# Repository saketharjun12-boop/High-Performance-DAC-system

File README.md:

# High-Performance Mixed-Signal Headphone DAC

**AK4191EQ + AK4499EX + ESP32-S3 | KiCad | Low-Noise Power | High-Impedance Headphones**

A custom mixed-signal headphone DAC/amplifier designed around the **AK4191EQ digital modulator** and **AK4499EX DAC**, with a focus on low-noise analog power, current-to-voltage conversion, differential analog processing, and high-impedance headphone drive.

> **Project status:** PCB routing is **not complete**. Routing is currently complete **through Stage 2 only**. Later analog/output and remaining power-routing sections are still in progress.

---

## Project Overview

Primary signal chain:

```text
Digital Source
    |
AK4191EQ Digital Modulator
    |
AK4499EX DAC
    |
OPA1612 I/V Conversion
    |
Low-Pass / Differential Summing
    |
OPA1622 Headphone Driver
    |
Output Mute Relay
    |
6.35 mm TRS Headphone Jack
```

Control is provided by an **ESP32-S3**, including I2C configuration and future power-sequencing / relay-control functionality.

---

## Main Components

| Function | Component |
|---|---|
| Digital modulator | AK4191EQ |
| DAC | AK4499EX |
| Controller | ESP32-S3 |
| I/V conversion | OPA1612 |
| Headphone output stage | OPA1622 |
| 5 V to 5.8 V boost | TPS610891 |
| Ultra-low-noise 5VA LDO | LT3045 |
| Bipolar analog supply | TPS65131 |
| Output muting | DPDT relay |
| Output connector | 6.35 mm TRS jack |

---

## Current Project Status

- [x] Overall architecture defined
- [x] Major components selected
- [x] AK4191EQ / AK4499EX architecture
- [x] I/V conversion stage
- [x] Differential / headphone output stage
- [x] Relay-based output mute
- [x] 5VA power architecture
- [x] +/-15 V rail architecture
- [x] Initial power budget
- [x] TPS610891 design calculations
- [x] LT3045 calculations
- [x] Initial +/-15 V / headphone-load budget
- [x] Initial trace-width and via-sizing methodology
- [x] PCB routing through **Stage 3**
- [ ] Remaining PCB routing
- [ ] Final ERC / DRC
- [ ] Final BOM freeze
- [ ] Gerber generation
- [ ] Fabrication
- [ ] Assembly
- [ ] Board bring-up
- [ ] Electrical validation
- [ ] Audio measurements

---

# Power Architecture

```text
USB-C 5 V
   |
   +---- TPS610891 ----> 5.8 V ----> LT3045 ----> 5VA
   |
   +---- TPS65131 ----> +15 V / -15 V
   |
   +---- 3.3 V Regulator ----> ESP32-S3 / clocks / logic
   |
   +---- 1.2 V Regulator ----> AK4191EQ core
```

The **5VA** rail is reserved for the AK4499EX analog/reference supply domains.

---

# Power Budget

The power budget is used to verify regulator capability, estimate upstream USB-C current, and provide starting values for power-trace and via sizing.

## 5VA Analog Rail

| Device / Supply Domain | Typical Current |
|---|---:|
| AK4499EX VDDL + VDDR | 18 mA |
| AK4499EX VREFHL + VREFHR | 46 mA |
| AK4499EX AVDD | 3 mA |
| **AK4499EX subtotal** | **67 mA** |
| LT3045 operating-current provision | ~3 mA |
| **Approximate subtotal** | **~70 mA** |

30% design margin:

```text
70 mA x 1.30 = 91 mA
```

Rounded target:

**5VA design current = 100 mA**

The LT3045 is rated for **500 mA**, so the present load estimate has substantial current margin.

## +15 V and -15 V Rails

| Device | Approximate Current |
|---|---:|
| OPA1622, two channels | 6.76 mA |
| OPA1612 stages | 18 mA |
| **Quiescent subtotal** | **24.76 mA** |

The headphone load adds output-stage rail current. A provisional design target of **75 mA per rail** is derived below.

## 3.3 V Rail

| Component / Function | Peak / Estimated Current |
|---|---:|
| ESP32-S3-MINI-1U peak RF transient assumption | 355 mA |
| AK4191EQ 3.3 V domain(s) | ~5 mA |
| Master-clock oscillators | ~20 mA total |
| 74LVC1G3157 MUX | ~2 mA |
| Pull-ups / passive leakage | ~3 mA |
| **Estimated peak subtotal** | **385 mA** |

Using 50% margin for ESP32 burst current:

```text
385 mA x 1.5 = 577.5 mA
```

Rounded target:

**3.3 V design current = 600 mA**

## 1.2 V Rail

AK4191EQ DVDD core:

- Typical: ~18 mA
- Max / peak design value: ~25 mA

30% margin:

```text
25 mA x 1.30 = 32.5 mA
```

Rounded target:

**1.2 V design current = 40 mA**

---

# TPS610891 Boost Converter Calculations

The TPS610891 creates approximately **5.8 V** from the USB-C 5 V input so the LT3045 has headroom to regulate to 5.0VA.

## Design Targets

| Parameter | Value |
|---|---:|
| VIN | 5.0 V nominal |
| VOUT | 5.8 V |
| IOUT | 100 mA |
| fSW | ~2 MHz |
| Provisional efficiency | 85% |
| Provisional inductor | 2.2 uH |

## Feedback Divider

The PWM feedback reference is approximately 1.212 V.

```text
VOUT = VREF(1 + R1/R2)
```

Choose:

```text
R2 = 100 kOhm
```

Then:

```text
R1 = R2(VOUT/VREF - 1)
R1 = 100k(5.8/1.212 - 1)
R1 ~= 378.5 kOhm
```

Practical selection:

- **R1 ~= 379 kOhm**
- **R2 = 100 kOhm**

## Switching-Frequency Resistor

Using the TPS610891 frequency-setting equation:

```text
RFREQ = 4(1/fSW - tDELAY*VOUT/VIN) / CFREQ
```

with:

```text
fSW = 2 MHz
tDELAY = 86 ns
CFREQ = 24 pF
VOUT = 5.8 V
VIN = 5.0 V
```

Calculated:

**RFREQ ~= 66.7 kOhm**

## Average Inductor Current

```text
IDC = (VOUT*IOUT)/(VIN*eta)
IDC = (5.8*0.1)/(5*0.85)
IDC ~= 136.5 mA
```

## Inductor Ripple Current

```text
IPP = 1 / [L(1/(VOUT-VIN) + 1/VIN)fSW]
```

For L = 2.2 uH:

**IPP ~= 157 mA p-p**

## Peak Inductor Current

```text
IL,peak = IDC + IPP/2
IL,peak = 136.5 mA + 78.5 mA
IL,peak ~= 215 mA
```

Worst-case inductance check using a 30% reduction:

```text
Lmin = 2.2 uH x 0.7 = 1.54 uH
```

A shielded power inductor rated around **1 A or higher** provides generous margin relative to the present calculated peak.

## Equivalent Output Load Resistance

```text
RO = VOUT/IOUT = 5.8/0.1 = 58 Ohm
```

**RO = 58 Ohm**

## Duty Cycle

Using the small-signal equation:

```text
D = 1 - (VIN*eta)/VOUT
D = 1 - (5*0.85)/5.8
D ~= 0.267
```

**D ~= 26.7%**

## Provisional Compensation Assumptions

```text
CO effective = 45 uF
RESR = 3 mOhm
L = 2.2 uH
fSW = 2 MHz
eta = 85%
IOUT = 100 mA
```

These values are provisional until the final capacitor and inductor part numbers are selected.

## Output Pole

```text
fP = 2/(2*pi*RO*CO)
fP ~= 122 Hz
```

## ESR Zero

```text
fESRZ = 1/(2*pi*RESR*CO)
fESRZ ~= 1.18 MHz
```

## Right-Half-Plane Zero

```text
fRHPZ = RO(1-D)^2/(2*pi*L)
fRHPZ ~= 2.25 MHz
```

## Crossover Frequency

Guideline:

```text
fC <= min(fSW/10, fRHPZ/5)
```

```text
fSW/10 = 200 kHz
fRHPZ/5 ~= 450 kHz
```

Provisional crossover:

**fC = 200 kHz**

## Compensation Resistor R5

```text
R5 = [2*pi*VOUT*Rsense*fC*CO] / [(1-D)*VREF*GEA]
```

Using:

```text
Rsense = 0.08 Ohm
VREF = 1.212 V
GEA = 190 uS
```

Calculated:

**R5 ~= 155.5 kOhm**

Practical provisional values:

- 154 kOhm
- 158 kOhm

## Compensation Capacitor C5

```text
C5 = RO*CO/(2*R5)
C5 ~= 8.39 nF
```

Practical provisional value:

**C5 ~= 8.2 nF**

## Compensation Capacitor C6

```text
C6 = RESR*CO/R5
C6 ~= 0.87 pF
```

Because the calculated value is below 10 pF:

**C6 = DNP / Open**

> The compensation network is provisional and should be recalculated using the final inductor, effective output capacitance, capacitor ESR, switching frequency, efficiency, and load.

---

# LT3045 5VA Rail Calculations

Architecture:

```text
5.8 V --> LT3045 --> 5.0VA
```

## SET Resistor

The SET pin sources approximately 100 uA.

```text
RSET = VOUT/ISET
RSET = 5.0/(100 uA)
RSET = 50 kOhm
```

Practical precision value:

**RSET = 49.9 kOhm**

## LDO Dissipation

At the 100 mA design target:

```text
PLDO = (VIN-VOUT)IOUT
PLDO = (5.8-5.0)(0.1)
PLDO = 0.08 W
```

## Power-Good Divider

The PGFB comparator threshold is approximately 300 mV.

Desired Power Good threshold:

```text
VTRIP ~= 4.5 V
```

Choose:

```text
RBOTTOM = 49.9 kOhm
```

Then:

```text
RTOP = RBOTTOM(VTRIP/VPGFB - 1)
RTOP = 49.9k(4.5/0.3 - 1)
RTOP ~= 698.6 kOhm
```

Practical values:

- **RTOP ~= 700 kOhm**
- **RBOTTOM = 49.9 kOhm**

## PG Pull-Up

For ESP32 3.3 V logic:

**RPG = 10 kOhm to 3.3 V**

## Provisional LT3045 Capacitors

- Input: **10 uF + 100 nF**
- SET: **4.7 uF** optional low-noise capacitor
- Output: **22 uF + 100 nF**

Final values should be verified against the final LT3045 implementation.

---

# TPS65131 +/-15 V Rail Calculations

Current design targets:

- **+15 V, 75 mA**
- **-15 V, 75 mA**

## Output Power

```text
POUT = 15I+15 + 15I-15
POUT = 15(0.075) + 15(0.075)
POUT = 2.25 W
```

## 5 V Input-Power Estimate

Assume provisional efficiency:

```text
eta = 80%
```

Then:

```text
PIN = POUT/eta
PIN = 2.25/0.8
PIN = 2.8125 W
```

Input current from 5 V:

```text
IIN,5V = PIN/5
IIN,5V = 2.8125/5
IIN,5V ~= 563 mA
```

**Provisional TPS65131 5 V input requirement ~= 0.56 A**

---

# Headphone Load Calculations

Target class: high-impedance headphones such as a nominal **300 Ohm** load.

The AK4499EX documentation indicates approximately:

- **4.6 Vrms** after individual I/V conversion around signal common
- approximately **9.2 Vrms** after external differential summing

## RMS Headphone Current

```text
IRMS = VRMS/RHP
IRMS = 9.2/300
IRMS ~= 30.7 mA/channel
```

## Peak Current

```text
IPEAK = sqrt(2)*IRMS
IPEAK ~= 43.4 mA/channel
```

## Output Power

```text
POUT = VRMS^2/RHP
POUT = 9.2^2/300
POUT ~= 0.282 W/channel
```

## Approximate Rail-Current Contribution

For a sinusoidal class-AB approximation:

```text
Irail,load ~= IPEAK/pi
Irail,load ~= 13.8 mA/channel
```

Stereo:

```text
Irail,load,stereo ~= 27.6 mA/rail
```

Add amplifier quiescent current:

```text
24.76 + 27.6 = 52.36 mA/rail
```

Apply 30% margin:

```text
52.36 x 1.30 = 68.1 mA/rail
```

Rounded design target:

**75 mA per rail**

---

# Trace Width Calculations

Power-trace width is based on current, copper thickness, route length, acceptable voltage drop, temperature rise, and fabrication limits.

Copper resistivity:

```text
rho ~= 1.72e-8 Ohm*m
```

For 1 oz copper:

```text
t ~= 35 um
```

## Trace Resistance

```text
Rtrace = rho*L/(w*t)
```

## Voltage Drop

```text
Vdrop = I*Rtrace
```

## Power Loss

```text
Ploss = I^2*Rtrace
```

## Width From Voltage-Drop Requirement

```text
w = rho*L*I/(t*Vdrop,max)
```

## 5VA Example

Assume:

```text
I = 0.1 A
L = 50 mm = 0.05 m
Vdrop,max = 5 mV = 0.005 V
t = 35 um
```

Calculated:

```text
w ~= 0.49 mm
```

Practical provisional width:

**5VA = 0.50 mm**

## +/-15 V Example

Using:

```text
I = 75 mA
L = 50 mm
Vdrop,max = 5 mV
```

Calculated width is approximately 0.37 mm.

Practical provisional choice:

**+15 V / -15 V = 0.50 mm**

## 3.3 V Main Distribution

With a 600 mA design target, the main 3.3 V trunk is provisionally assigned:

**3.3 V main = ~0.8 mm**

Individual low-current branches do not need to remain 0.8 mm.

## USB 5 V

Provisional initial class:

**USB 5 V = 1.0-1.2 mm**

## Headphone Output

The 300 Ohm load current is modest, so the wider trace primarily reduces added series resistance and provides robust routing.

**Headphone output = ~0.8 mm**

---

# Via Sizing

## Standard Signal Via

```text
Diameter: 0.60 mm
Drill:    0.30 mm
```

Used for digital signals, I2C, I2S, ordinary analog signals, ground stitching, and low-current branches.

## Power Via

```text
Diameter: 0.80 mm
Drill:    0.40 mm
```

Used for 5VA, +/-15 V, and main 3.3 V power transitions.

## Higher-Current USB Via

```text
Diameter: 1.00 mm
Drill:    0.50 mm
```

or multiple smaller vias in parallel.

Multiple vias are preferred where higher current or lower inductance is desired.

---

# Net Classes

| Net Class | Clearance | Width | Via | Drill |
|---|---:|---:|---:|---:|
| Signal | 0.20 mm | 0.20 mm | 0.60 mm | 0.30 mm |
| Clock | 0.20 mm | 0.20 mm | 0.60 mm | 0.30 mm |
| I2S | 0.20 mm | 0.20 mm | 0.60 mm | 0.30 mm |
| Analog Signal | 0.20 mm | 0.20-0.25 mm | 0.60 mm | 0.30 mm |
| 5VA | 0.20 mm | 0.50 mm | 0.80 mm | 0.40 mm |
| +15 V | 0.20 mm | 0.50 mm | 0.80 mm | 0.40 mm |
| -15 V | 0.20 mm | 0.50 mm | 0.80 mm | 0.40 mm |
| 3V3 Main | 0.20 mm | ~0.80 mm | 0.80 mm | 0.40 mm |
| 1V2 | 0.20 mm | 0.30-0.50 mm | 0.60 mm | 0.30 mm |
| USB Power | 0.20-0.25 mm | 1.0-1.2 mm | 1.00 mm | 0.50 mm |
| Headphone Out | 0.20 mm | 0.80 mm | 0.80 mm | 0.40 mm |

These values should be checked against the final PCB manufacturer's design rules.

---

# Critical Signal Lengths

| Connection | Target |
|---|---:|
| AK4499EX IOUT to OPA1612 input | ideally <5-10 mm |
| OPA1612 feedback loop | ideally <5 mm |
| OPA1622 feedback / summing network | ideally <5-10 mm |
| 100 nF decoupling capacitor | approximately 1-3 mm from supply pin where practical |
| TPS610891 SW to inductor | minimum practical length |
| TPS65131 switch nodes | minimum practical length |
| LT3045 SET / OUTS | preferably <5-10 mm |
| MCLK | preferably <25-30 mm |
| BCLK / LRCK / SDATA | short; ~10 mm BCLK is excellent |

---

# Repository Folders

```text
High_Performance_DAC_Portfolio/
|
|-- README.md
|-- PCB_Files/
|-- Schematics/
|-- Images/
|-- Handwritten_Calculations/
|-- Datasheets/
|-- BOM/
`-- Gerbers/
```

## Schematic Images and PCB progress

## Total Circuit

## Stage 1

## Stage 2

## Stage 3

## Stage 4

## USB-C Interface

## Boost Inverter and Boost Regulator

## PCB progress Stage 1 and Stage 2

---

# Planned Validation

After fabrication:

- Verify 5.8 V boost output
- Verify 5VA regulation
- Measure 5VA ripple
- Measure +15 V and -15 V ripple
- Verify startup sequencing
- Verify Power Good behavior
- Verify relay mute timing
- Measure DAC DC offsets
- Verify maximum headphone output
- Measure frequency response
- Measure FFT / noise floor
- Measure THD+N
- Measure output impedance
- Evaluate thermal performance

---

# Future Work

- Complete PCB routing after Stage 2
- Recalculate power-trace voltage drop using actual routed lengths
- Freeze exact capacitor and inductor manufacturer part numbers
- Recalculate TPS610891 compensation using final effective capacitance and ESR
- Perform final regulator thermal checks
- Run ERC and DRC
- Generate Gerbers
- Fabricate and assemble the PCB
- Perform bring-up and measurement
- Add measurement plots and final PCB renders to this README

---

# Disclaimer

This repository documents an **in-progress engineering project**.

The present PCB routing is not complete, and the design has not yet been fabricated or electrically validated. Several calculated values are provisional and will be updated after the final BOM, PCB routing, and measured prototype data are available.

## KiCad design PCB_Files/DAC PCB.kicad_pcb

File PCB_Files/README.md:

Place KiCad PCB/project files here.

Current PCB routing is incomplete and only complete through Stage 3.

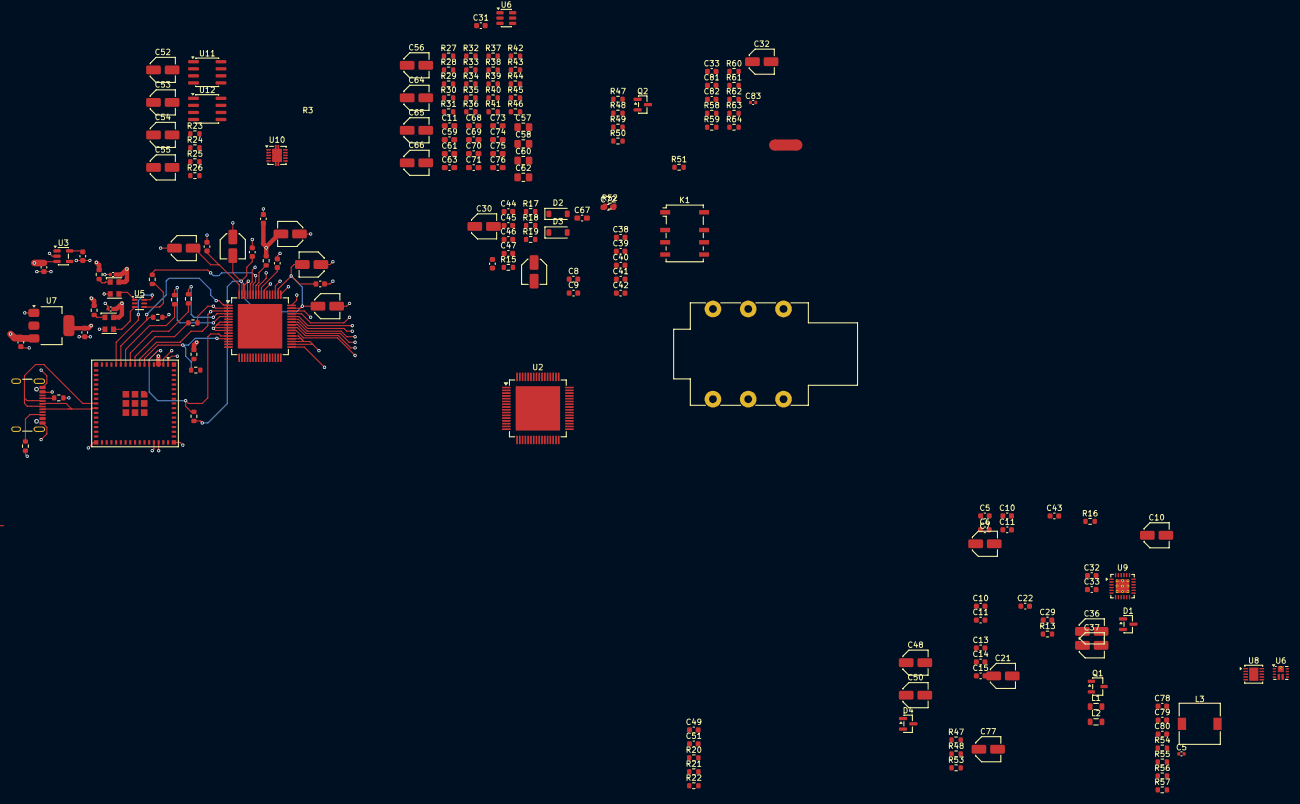
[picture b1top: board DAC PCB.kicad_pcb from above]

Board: 4 copper layers, 184 parts (0 on the bottom side), 109 nets.

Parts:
C1, C2, C5#2: 0.1uF; C_0402_1005Metric
C3, C4, C5, C6, C8, C9, C10, C10#2, C11#2, C11#3, C12, C14, C16: 1uF; C_0603_1608Metric
C7, C10#3: 1uF; C_Elec_4x5.4
C11, C59, C61, C63: 100nF; C_0603_1608Metric_Pad1.08x0.95mm_HandSolder
C13, C15: 10uF; C_0603_1608Metric
C17, C19, C21, C26, C28: 10F; C_Elec_4x5.4
C18, C20, C22, C24, C27, C29, C33#2: 0.1F; C_0603_1608Metric
C23, C30, C32#2, C36, C50, C52, C54: 10uF; C_Elec_4x5.4
C25: 22F; C_0603_1608Metric
C31, C33, C34, C49, C51, C81: 0.1uF; C_0603_1608Metric
C32: 10F; C_0603_1608Metric
C35, C48: 2200uF; C_Elec_4x5.4
C37, C53, C55, C77: 0.1uF; C_Elec_4x5.4
C38, C40, C46: 4.7uF; C_0603_1608Metric
C39: 100nF; C_0603_1608Metric
C41, C45, C78, C79, C80, C82: 22uF; C_0603_1608Metric
C42: 6.8pF; C_0603_1608Metric
C43: 220nF; C_0603_1608Metric
C44: 7.5pF; C_0603_1608Metric
C47: 10nF; C_0603_1608Metric
C56, C64, C65, C66: 180pF; C_Elec_4x5.4
C57, C58, C60, C62: 10uF; C_0805_2012Metric_Pad1.18x1.45mm_HandSolder
C67, C68, C69, C70, C71, C72: 1nF; C_0603_1608Metric_Pad1.08x0.95mm_HandSolder
C73, C74, C75, C76: 470pF; C_0603_1608Metric_Pad1.08x0.95mm_HandSolder
C83: 8.5nF; C_0402_1005Metric
D1, D4: BZX84Cxx; SOT-23
D2, D3: D_Schottky; D_SOD-123
J1: USB_C_Receptacle_USB2.0_16P; USB_C_Receptacle_GCT_USB4105-xx-A_16P_TopMnt_Horizontal
J2: AudioJack3_Switch; Jack_6.35mm_Neutrik_NMJ6HHD2_Horizontal
K1: Relay_DPDT; Relay_DPDT_Omron_G6K-2F-Y
L1, L2: 4.7uH; L_0805_2012Metric
L3: 2.2uH; L_7.3x7.3_H4.5
NT1: NetTie_2; NetTie-2_SMD_Pad2.0mm
Q1: Q_PMOS_GSD; SOT-23-3
Q2: MMBT3904; SOT-23
R1, R2, R7, R8, R14, R21: 4700; R_0603_1608Metric
R3, R4, R5, R10: 33; R_0603_1608Metric
R6, R9, R13, R20, R22, R47, R48, R53, R63: 10000; R_0603_1608Metric
R11, R12: 5100; R_0603_1608Metric
R15, R32, R34, R37, R38: 100; R_0603_1608Metric
R16, R19: 1M; R_0603_1608Metric
R17: 130k; R_0603_1608Metric
R18: 121.2k; R_0603_1608Metric
R23, R24, R25, R26, R41, R42, R45, R46: 2000; R_0603_1608Metric
R27, R28, R29, R30: 360; R_0603_1608Metric
R31, R33, R35, R36: 500; R_0603_1608Metric
R39, R40, R43, R44: 5000; R_0603_1608Metric
R47#2, R48#2, R51, R52: 2.2; R_0603_1608Metric
R49: 2200; R_0603_1608Metric
R50: 100000; R_0603_1608Metric
R54: 66.8k; R_0603_1608Metric
R55: 378.5k; R_0603_1608Metric
R56: 100k; R_0603_1608Metric
R57: 1.03M; R_0603_1608Metric
R58: 30.1k; R_0603_1608Metric
R59: 249; R_0603_1608Metric
R60: 50; R_0603_1608Metric
R61: 49.9k; R_0603_1608Metric
R62: 700k; R_0603_1608Metric
R64: 150k; R_0603_1608Metric
U1, U2: Texas_TQFP-64-1EP_10x10mm_P0.5mm_EP8x8mm_Mask4.44x4.44mm
U3: AP2112K-1.2; SOT-23-5
U4: ESP32-S3-MINI-1U; ESP32-S2-MINI-1U
U5: 74LVC1G3157; SOT-363_SC-70-6
U6: TPS610891; Texas_VQFN-RNR0011A-11
U6#2: MCP4725xxx-xCH; SOT-23-6
U7: AMS1117-3.3; SOT-223-3_TabPin2
U8: LT3045xDD; DFN-10-1EP_3x3mm_P0.5mm_EP1.65x2.38mm
U9: TPS65131RGE; VQFN-24-1EP_4x4mm_P0.5mm_EP2.45x2.45mm_ThermalVias
U10: OPA1622; Texas_S-PVSON-N10
U11, U12: OPA1612AxD; SOIC-8_3.9x4.9mm_P1.27mm
Y1, Y2: XO32; Oscillator_SMD_EuroQuartz_XO32-4Pin_3.2x2.5mm

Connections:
+1.2V: C16.1, C17.2, C18.2, U1.64 (DVDD), U3.5 (VOUT)
+1.8V: C6.1, C7.2, C8.2, C9.2, C10#3.2, C13.1, C14.1, C15.1, C19.2, C20.2, C26.2, C27.2, C28.1, C29.1, C30.2, C31.2, C32#2.1, C33.1, C34.1, C35.1, C36.2, C37.2, C48.1, C49.1, C50.2, C51.2, C52.1, C53.1, C54.1, C55.1, C68.2, C69.1, C71.2, C72.1, C73.1, C75.1, C81.1, C82.2, D1.1 (A), D4.1 (A), J2.S, NT1.2, Q2.2 (E), R1.1, R2.1, R20.2, R21.1, R24.2, R26.2, R42.1, R45.1, R50.1, R58.2, R59.2, R60.2, R61.2, U1.47 (TVDD4), U1.50 (TVDD3), U1.63 (TVDD1), U2.2 (TVDD), U2.21 (VREFHR), U2.22 (VREFHR), U2.23 (VREFHR), U2.27 (VSSR), U2.28 (VSSR), U2.29 (VSSR), U2.34 (DEV1), U2.47 (DEV2), U2.52 (VSSL), U2.53 (VSSL), U2.54 (VSSL), U2.55 (VREFLL), U2.56 (VREFLL), U2.57 (VREFLL), U2.62 (AVSS), U2.64 (DVDD), U8.8 (GND), U8.11 (GND), U10.3 (GND)
+3.3V: C1.2, C2.2, C4.1, C11#3.1, C23.2, C24.2, R7.1, R8.1, R9.1, R13.1, R14.1, R53.1, R63.1, U4.3 (3V3), U7.2 (VO), Y1.4 (V+), Y2.4 (V+)
+5V: C3.1, C5.1, C10#2.1, C12.1, C32.2, C33#2.2, C40.1, C78.1, J1.A4 (VBUS), J1.A9 (VBUS), J1.B4 (VBUS), J1.B9 (VBUS), L3.1, Q1.2 (S), R15.1, U3.1 (VIN), U3.3 (EN), U6.9 (VIN), U6#2.3 (VDD), U7.3 (VI), U9.5 (INN), U9.6 (INN)
+5VA: C30.1, C31.1, C34.2, C35.2, C36.1, C37.1, C48.2, C49.2, C50.1, C51.1, C81.2, C82.1, D1.3 (K), D4.3 (K), R23.1, R25.1, R60.1, R62.1, U2.24 (VREFLR), U2.25 (VREFLR), U2.26 (VREFLR), U2.30 (VDDR), U2.31 (VDDR), U2.32 (VDDR), U2.49 (VDDL), U2.50 (VDDL), U2.51 (VDDL), U2.58 (VREFHL), U2.59 (VREFHL), U2.60 (VREFHL), U2.61 (AVDD), U6#2.1 (VOUT), U8.9 (OUTS), U8.10 (OUT)
+15V: C11.1, C41.1, C42.1, C57.1, C60.1, C61.1, D2.1 (K), R16.2, U9.23 (VPOS), U10.2 (V+), U10.8 (EN), U11.8 (V+), U12.8 (V+)
-15V: C44.2, C45.1, C58.1, C59.1, C62.1, C63.1, D3.2 (A), R19.1, U9.15 (VNEG), U10.4 (V-), U10.11 (V-), U11.4 (V-), U12.4 (V-)
/BCKO: U1.46 (BCKO), U2.4 (BCK)
/BICK: R3.2, U1.2 (BICK/DCLK/BCK)
/Base: Q2.1 (B), R49.2, R50.2
/D+: J1.A6 (D+), J1.B6 (D+), U4.24 (USB_D+)
/D-: J1.A7 (D-), J1.B7 (D-), U4.23 (USB_D-)
/ILeft+ve: R28.2, U2.42 (IOUTLP)
/ILeft-ve: R27.2, U2.45 (IOUTLN)
/IRight+ve: R30.2, U2.39 (IOUTRP)
/IRight-ve: R29.2, U2.36 (IOUTRN)
/LRCK: R4.2, U1.4 (LRCK/DSDR/DINR)
/Left+VE: C64.1, U2.43 (OPINLP), U11.6 (-)
/Left-VE: C56.1, U2.44 (OPINLN), U11.2 (-)
/MCLKEQ: R10.1, U1.59 (MCLK)
/MCLKO: U1.51 (MCLKO), U2.63 (MCLK)
/MCLKi: U4.12 (IO8), U5.6
/Muten: R22.1, U1.33 (MUTEN), U2.16 (MUTEN), U4.19 (IO15)
/PDN: R6.1, U1.1 (PDN), U4.11 (IO7)
/PG: R63.2, U4.21 (IO17), U8.4 (PG)
/Right+VE: C66.1, U2.38 (OPINRP), U12.6 (-)
/Right-VE: C65.1, U2.37 (OPINRN), U12.2 (-)
/SCL: R2.2, U1.12 (CCLK/SCL), U2.14 (LRSEL0/CCLK/SCL), U4.5 (IO1), U6#2.5 (SCL)
/SDA: R1.2, U1.13 (CDTI/SDA), U2.15 (LRSEL1/CDTI/SDA), U4.6 (IO2), U6#2.4 (SDA)
/SDATA: U1.3 (SDATA/DSDL/DINL), U4.7 (IO3)
/SDATA2: R5.2, U1.5 (SDTA2/DINL2)
/TVDD2: C21.1, C22.1, U1.60 (TVDD2)
/VOUTLN: C64.2, R28.1, R33.2, U11.7
/VOUTLP: C56.2, R27.1, R31.2, U11.1
/VOUTRP: C65.2, C66.2, R29.1, R30.1, R35.2, R36.2, U12.1, U12.7
/VoffL: C54.2, C55.2, R25.2, R26.1, U2.48 (VCOML), U11.3 (+), U11.5 (+)
/VoffR: C52.2, C53.2, R23.2, R24.1, U2.33 (VCOMR), U12.3 (+), U12.5 (+)
/in1: U1.45 (MBD1), U2.5 (MBD1)
/in2: U1.44 (MBD2), U2.6 (MBD2)
/in3: U1.43 (MBD3), U2.7 (MBD3)
/in4: U1.42 (MBD4), U2.8 (MBD4)
/in5: U1.41 (MBD5), U2.9 (MBD5)
/in6: U1.40 (MBD6), U2.10 (MBD6)
/in7: U1.39 (MBD7), U2.11 (MBD7)
GND: C1.1, C2.1, C3.2, C4.2, C5.2, C6.2, C10#2.2, C11.2, C11#3.2, C12.2, C16.2, C17.1, C18.1, C19.1, C20.1, C21.2, C22.2, C23.1, C24.1, C25.2, C26.1, C27.1, C28.2, C29.2, C32.1, C33#2.1, C38.2, C39.2, C40.2, C41.2, C43.2, C45.2, C46.2, C47.2, C57.2, C58.2, C59.2, C60.2, C61.2, C62.2, C63.2, C77.2, C78.2, C79.2, C80.2, C83.2, J1.A1 (GND), J1.A12 (GND), J1.B1 (GND), J1.B12 (GND), L2.1, NT1.1, R6.2, R11.2, R12.2, R17.1, R22.2, R47.1, R48.1, R56.2, R57.2, U1.7 (WCK), U1.8 (DSDL2), U1.9 (DSDR2), U1.10 (DCLK), U1.11 (CSN), U1.17 (PROG), U1.18 (AMUTE), U1.19 (CAD0), U1.20 (CAD1), U1.22 (TST2), U1.23 (TST1), U1.34 (NC), U1.35 (NC), U1.36 (NC), U1.37 (NC), U1.38 (NC), U1.48 (DVSS4), U1.49 (DVSS3), U1.55 (TST), U1.57 (PVSS), U1.61 (DVSS2), U1.62 (DVSS1), U3.2 (GND), U4.1 (GND), U4.2 (GND), U4.42 (GND), U4.43 (GND), U4.46 (GND), U4.47 (GND), U4.48 (GND), U4.49 (GND), U4.50 (GND), U4.51 (GND), U4.52 (GND), U4.53 (GND), U4.54 (GND), U4.55 (GND), U4.56 (GND), U4.57 (GND), U4.58 (GND), U4.59 (GND), U4.60 (GND), U4.61 (GND), U4.62 (GND), U4.63 (GND), U4.64 (GND), U4.65 (GND), U6.5 (GND), U6#2.2 (VSS), U6#2.6 (A0), U7.1 (GND), U9.2 (PGND), U9.3 (PGND), U9.19 (AGND), U9.25 (EP), Y1.2 (GND), Y2.2 (GND)
unnamed: C67.1, R31.1, R32.2
unnamed: C67.2, R33.1, R34.2
unnamed: C68.1, R32.1, R39.2
unnamed: C69.2, R34.1, R40.2
unnamed: C70.1, R35.1, R37.2
unnamed: C70.2, R36.1, R38.2
unnamed: C71.1, R37.1, R43.2
unnamed: C72.2, R38.1, R44.2
unnamed: C74.2, R41.1, R47#2.2, U10.9
unnamed: C76.2, R46.1, R48#2.2, U10.7
unnamed: C83.1, R64.2
unnamed: D2.2 (A), L1.2, U9.1 (INP), U9.24 (INP)
unnamed: D3.1 (K), L2.2, U9.13 (OUTN), U9.14 (OUTN)
unnamed: J1.A5 (CC1), R11.1
unnamed: J1.B5 (CC2), R12.1
unnamed: J2.R, R52.1
unnamed: J2.T, R51.1
unnamed: C38.1, L1.1, Q1.3 (D)
unnamed: Q1.1 (G), U9.7 (BSW)
unnamed: R10.2, U5.4
unnamed: R13.2, U1.21 (I2C)
unnamed: R14.2, U1.58 (PVDD)
unnamed: C25.1, U1.56 (VCOM)
unnamed: R47.2, U2.18 (DSEL2/CAD1)
unnamed: C13.2, C14.2, C15.2, U2.1 (DVSS)
unnamed: C10#3.1, U2.46 (EXTCLN)
unnamed: C9.1, U2.41 (EXTCLP)
unnamed: C7.1, U2.35 (EXTCRN)
unnamed: C8.1, U2.40 (EXTCRP)
unnamed: R20.1, U2.19 (PSN)
unnamed: R48.2, U2.17 (SC/CAD0)
unnamed: R21.2, U2.20 (VTSEL/I2C)
unnamed: C77.1, R53.2, U4.45 (EN)
unnamed: R9.2, U4.4 (IO0)
unnamed: R3.1, U4.8 (IO4)
unnamed: R4.1, U4.9 (IO5)
unnamed: R5.1, U4.10 (IO6)
unnamed: R49.1, U4.20 (IO16)
unnamed: C5#2.2, U6.10 (BOOT)
unnamed: R64.1, U6.4 (COMP)
unnamed: C79.1, U6.7 (EN)
unnamed: R55.2, R56.1, U6.3 (FB)
unnamed: R54.2, U6.1 (FSW)
unnamed: R57.1, U6.8 (ILIM)
unnamed: C5#2.1, L3.2, R54.1, U6.11 (SW)
unnamed: C80.1, U6.2 (VCC)
unnamed: C32#2.2, C33.2, R55.1, U6.6 (VOUT), U8.1 (IN), U8.2 (IN), U8.3 (EN/UV)
unnamed: R59.1, U8.5 (ILIM)
unnamed: R61.1, R62.2, U8.6 (PGFB)
unnamed: R58.1, U8.7 (SET)
unnamed: C46.1, U9.18 (CN)
unnamed: C47.1, U9.21 (CP)
unnamed: C39.1, R15.2, U9.4 (VIN), U9.8 (ENP), U9.9 (PSP), U9.10 (ENN), U9.11 (PSN)
unnamed: C44.1, R18.1, R19.2, U9.16 (FBN)
unnamed: C42.2, R16.1, R17.2, U9.22 (FBP)
unnamed: C43.1, R18.2, U9.17 (VREF)
unnamed: C73.2, R39.1, R42.2, U10.1 (+)
unnamed: C74.1, R40.1, R41.2, U10.10 (-)
unnamed: C75.2, R43.1, R45.2, U10.5 (+)
unnamed: C76.1, R44.1, R46.2, U10.6 (-)
unnamed: R7.2, Y1.1 (EN)
unnamed: U5.3, Y1.3 (OUT)
unnamed: R8.2, Y2.1 (EN)
unnamed: U5.1, Y2.3 (OUT)
